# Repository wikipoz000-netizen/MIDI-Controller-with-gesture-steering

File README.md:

English below
# MIDI DJ Controller z kontrolą gestami

Projekt przedstawia autorski kontroler MIDI DJ wzbogacony o eksperymentalny system sterowania gestami. Urządzenie zostało opracowane w ramach pracy inżynierskiej na kierunku **Automatyka i Robotyka**.

## Opis projektu

Urządzenie łączy tradycyjne elementy kontrolera DJ (fadery, pokrętła, koła jog, przyciski) z warstwą bezdotykowego sterowania gestami opartą na ultradźwiękowych czujnikach odległości.

Kontroler komunikuje się z komputerem poprzez interfejs **USB-MIDI** i jest w pełni kompatybilny z oprogramowaniem DJ-skim, takim jak **Mixxx**.

## Sprzęt (Hardware)

Główne komponenty systemu:

* **Mikrokontroler:** Raspberry Pi Pico (RP2040)
* **Wejścia analogowe:** Multiplekser ADC (rozszerzenie liczby kanałów analogowych)
* **Wejścia cyfrowe:** Ekspander GPIO (dodatkowe wejścia dla przycisków)
* **Detekcja gestów:** Ultradźwiękowe czujniki odległości
* **Interfejs dotykowy:** Pojemnościowe czujniki dotyku
* **Konstrukcja:** Dedykowana płytka PCB oraz obudowa wykonana w technologii druku 3D

Pełna dokumentacja sprzętowa, schematy oraz projekty PCB znajdują się w katalogu `/hardware`.

## Oprogramowanie układowe (Firmware)

Firmware odpowiada za:

* Odczyt i filtrowanie sygnałów z wejść analogowych i cyfrowych.
* Skalowanie sygnałów i eliminację szumów.
* Interpretację danych z czujników na konkretne gesty.
* Generowanie komunikatów MIDI (**Note On/Off, Control Change, Pitch Bend**).
* Komunikację USB-MIDI o niskim opóźnieniu.

Kod źródłowy dostępny jest w katalogu `/firmware`.

## Integracja z oprogramowaniem

Kontroler został przetestowany z oprogramowaniem **Mixxx**. W repozytorium znajdują się niezbędne pliki mapowania MIDI (formaty `.xml` oraz `.js`).

## Zawartość repozytorium

* **Hardware:** Schematy ideowe i projekty płytek drukowanych.
* **Firmware:** Kod źródłowy mikrokontrolera.
* **Mapping:** Pliki konfiguracyjne MIDI dla oprogramowania DJ.
* **Dokumentacja:** Wyniki testów i specyfikacja techniczna.

---

# MIDI DJ Controller with Gesture Control

This project presents a custom-built MIDI DJ controller enhanced with an experimental gesture control system.  
It was developed as part of an engineering thesis in Robotics and Automation.

## Project Description

The device combines traditional DJ controller elements (faders, knobs, jog wheels, buttons) with a contactless gesture control layer based on ultrasonic distance sensors.

The controller communicates with a computer via USB-MIDI and is compatible with DJ software such as Mixxx.

## Hardware

Main components:

- Raspberry Pi Pico (RP2040)
- ADC multiplexer (for extended analog inputs)
- GPIO expander (for additional digital inputs)
- Ultrasonic distance sensors (gesture detection)
- Capacitive touch sensing
- Custom-designed PCB
- 3D-printed enclosure

All hardware schematics and PCB files are available in the `/hardware` directory.

## Firmware

The firmware is responsible for:

- Reading analog and digital inputs
- Signal filtering and scaling
- Gesture interpretation
- Generating MIDI messages (Note On/Off, Control Change, Pitch Bend)
- USB-MIDI communication

Source code is available in the `/firmware` directory.

## Software Integration

The controller was tested with Mixxx DJ software.  
The repository includes MIDI mapping files (XML and JS).

## Repository Contents

- Hardware schematics
- PCB design files
- Firmware source code
- MIDI mapping configuration
- Documentation and test results

---
## Licencja

Ten projekt jest udostępniony na licencji **Creative Commons Zero**. 
Więcej informacji w pliku [LICENSE](LICENSE).

## Autor

Wiktor Pozarzycki  
Praca inżynierska – 2026

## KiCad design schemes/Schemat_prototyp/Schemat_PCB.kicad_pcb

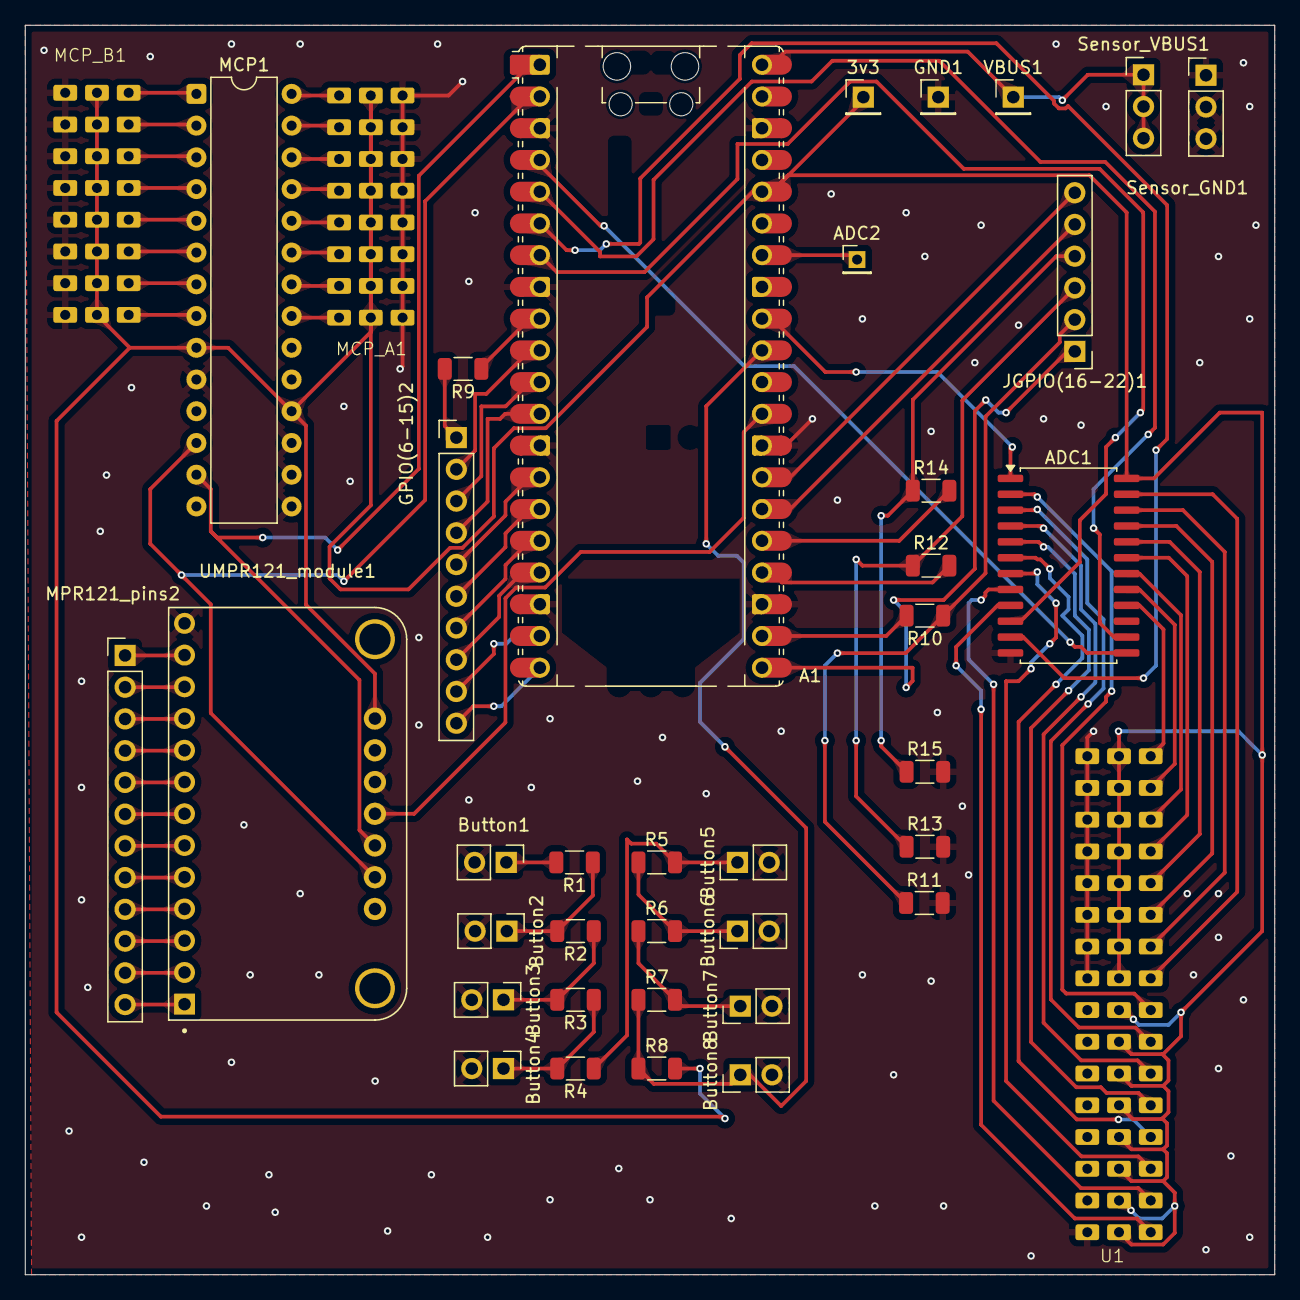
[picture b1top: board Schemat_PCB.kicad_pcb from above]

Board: 2 copper layers, 100.0 x 100.0 mm, 39 parts (0 on the bottom side), 84 nets.

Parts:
3v3: Conn_01x01_Pin; PinHeader_1x01_P2.54mm_Vertical
A1: RaspberryPi_Pico; RaspberryPi_Pico_Common_Unspecified
ADC1: CD74HC4067M; SOIC-24W_7.5x15.4mm_P1.27mm
ADC2: Conn_01x01_Pin; PinHeader_1x01_P2.00mm_Vertical
Button1, Button2, Button3, Button4, Button5, Button6, Button7, Button8: Conn_01x02_Pin; PinHeader_1x02_P2.54mm_Vertical
GND1: Conn_01x01_Pin; PinHeader_1x01_P2.54mm_Vertical
GPIO(6-15)2: Conn_01x10_Pin; PinHeader_1x10_P2.54mm_Vertical
JGPIO(16-22)1: Conn_01x06_Pin; PinHeader_1x06_P2.54mm_Vertical
MCP1: MCP23017_SP; DIP-28_W7.62mm
MCP_A1: PinHeader_3x8_2.54mm_MIRROR
MCP_B1: PinHeader_3x8_2.54mm_MIRROR
MPR121_pins2: Conn_01x12_Pin; PinHeader_1x12_P2.54mm_Vertical
R1: 15k; R_1206_3216Metric
R2: 7.5k; R_1206_3216Metric
R3: 4.7k; R_1206_3216Metric
R4: 3k; R_1206_3216Metric
R5: 2.2k; R_1206_3216Metric
R6: 1.6k; R_1206_3216Metric
R7: 1.2k; R_1206_3216Metric
R8: 10k; R_1206_3216Metric
R9: 330; R_1206_3216Metric
R10, R12, R14: 1k; R_1206_3216Metric
R11, R13, R15: 2k; R_1206_3216Metric
Sensor_GND1: Conn_01x03_Pin; PinHeader_1x03_P2.54mm_Vertical
Sensor_VBUS1: Conn_01x03_Pin; PinHeader_1x03_P2.54mm_Vertical
U1: PinHeader_3x16_2.54mm
UMPR121_module1: 1982; MODULE_1982
VBUS1: Conn_01x01_Pin; PinHeader_1x01_P2.54mm_Vertical

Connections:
GND: A1.3 (GND), A1.8 (GND), A1.13 (GND), A1.18 (GND), A1.23 (GND), A1.28 (GND), A1.38 (GND), ADC1.12 (GND), Button1.2, Button2.2, Button3.2, Button4.2, Button5.2, Button6.2, Button7.2, Button8.2, GND1.1, MCP1.10 (VSS), MCP1.15 (A0), MCP1.16 (A1), MCP1.17 (A2), MCP_A1.17 (GND), MCP_A1.18 (GND), MCP_A1.19 (GND), MCP_A1.20 (GND), MCP_A1.21 (GND), MCP_A1.22 (GND), MCP_A1.23 (GND), MCP_A1.24 (GND), MCP_B1.17 (GND), MCP_B1.18 (GND), MCP_B1.19 (GND), MCP_B1.20 (GND), MCP_B1.21 (GND), MCP_B1.22 (GND), MCP_B1.23 (GND), MCP_B1.24 (GND), R11.2, R13.2, R15.2, Sensor_GND1.1, Sensor_GND1.2, Sensor_GND1.3, U1.33 (GND), U1.34 (GND), U1.35 (GND), U1.36 (GND), U1.37 (GND), U1.38 (GND), U1.39 (GND), U1.40 (GND), U1.41 (GND), U1.42 (GND), U1.43 (GND), U1.44 (GND), U1.45 (GND), U1.46 (GND), U1.47 (GND), U1.48 (GND), UMPR121_module1.JP1_13 (GND), UMPR121_module1.JP2_3 (GND)
unnamed: 3v3.1, A1.36 (3V3), ADC1.24 (VCC), MCP1.9 (VDD), MCP1.18 (~RESET), MCP_A1.9 (VCC), MCP_A1.10 (VCC), MCP_A1.11 (VCC), MCP_A1.12 (VCC), MCP_A1.13 (VCC), MCP_A1.14 (VCC), MCP_A1.15 (VCC), MCP_A1.16 (VCC), MCP_B1.9 (VCC), MCP_B1.10 (VCC), MCP_B1.11 (VCC), MCP_B1.12 (VCC), MCP_B1.13 (VCC), MCP_B1.14 (VCC), MCP_B1.15 (VCC), MCP_B1.16 (VCC), R8.2, U1.17 (VCC), U1.18 (VCC), U1.19 (VCC), U1.20 (VCC), U1.21 (VCC), U1.22 (VCC), U1.23 (VCC), U1.24 (VCC), U1.25 (VCC), U1.26 (VCC), U1.27 (VCC), U1.28 (VCC), U1.29 (VCC), U1.30 (VCC), U1.31 (VCC), U1.32 (VCC), UMPR121_module1.JP2_1 (VIN)
unnamed: A1.1 (GPIO0), MCP1.13 (SDA), UMPR121_module1.JP2_5 (SDA)
unnamed: A1.2 (GPIO1), MCP1.12 (SCK), UMPR121_module1.JP2_6 (SCL)
unnamed: A1.4 (GPIO2), ADC1.13 (S3)
unnamed: A1.5 (GPIO3), ADC1.14 (S2)
unnamed: A1.6 (GPIO4), ADC1.11 (S1)
unnamed: A1.7 (GPIO5), ADC1.10 (S0)
unnamed: A1.9 (GPIO6), R9.1
unnamed: A1.10 (GPIO7), GPIO(6-15)2.2
unnamed: A1.11 (GPIO8), GPIO(6-15)2.3
unnamed: A1.12 (GPIO9), GPIO(6-15)2.4
unnamed: A1.14 (GPIO10), GPIO(6-15)2.5
unnamed: A1.15 (GPIO11), GPIO(6-15)2.6
unnamed: A1.16 (GPIO12), GPIO(6-15)2.7
unnamed: A1.17 (GPIO13), GPIO(6-15)2.8
unnamed: A1.19 (GPIO14), GPIO(6-15)2.9
unnamed: A1.20 (GPIO15), GPIO(6-15)2.10
unnamed: A1.21 (GPIO16), JGPIO(16-22)1.1
unnamed: A1.22 (GPIO17), R10.2
unnamed: A1.24 (GPIO18), R12.2
unnamed: A1.25 (GPIO19), R14.2
unnamed: A1.26 (GPIO20), JGPIO(16-22)1.5
unnamed: A1.27 (GPIO21), JGPIO(16-22)1.6
unnamed: A1.29 (GPIO22), UMPR121_module1.JP2_4 (ADDR)
unnamed: A1.31 (GPIO26_ADC0), Button8.1, R7.1, R8.1
unnamed: A1.32 (GPIO27_ADC1), ADC1.1 (COM)
unnamed: A1.34 (GPIO28_ADC2), ADC2.1
unnamed: A1.40 (VBUS), Sensor_VBUS1.1, Sensor_VBUS1.2, Sensor_VBUS1.3, VBUS1.1
unnamed: ADC1.9 (I0), U1.1 (A1)
unnamed: ADC1.8 (I1), U1.2 (A2)
unnamed: ADC1.7 (I2), U1.3 (A3)
unnamed: ADC1.6 (I3), U1.4 (A4)
unnamed: ADC1.5 (I4), U1.5 (A5)
unnamed: ADC1.4 (I5), U1.6 (A6)
unnamed: ADC1.3 (I6), U1.7 (A7)
unnamed: ADC1.2 (I7), U1.8 (A8)
unnamed: ADC1.23 (I8), U1.9 (A9)
unnamed: ADC1.22 (I9), U1.10 (A10)
unnamed: ADC1.21 (I10), U1.11 (A11)
unnamed: ADC1.20 (I11), U1.12 (A12)
unnamed: ADC1.19 (I12), U1.13 (A13)
unnamed: ADC1.18 (I13), U1.14 (A14)
unnamed: ADC1.17 (I14), U1.15 (A15)
unnamed: ADC1.16 (I15), U1.16 (A16)
unnamed: Button1.1, R1.2
unnamed: Button2.1, R1.1, R2.2
unnamed: Button3.1, R2.1, R3.2
unnamed: Button4.1, R3.1, R4.2
unnamed: Button5.1, R4.1, R5.2
unnamed: Button6.1, R5.1, R6.2
unnamed: Button7.1, R6.1, R7.2
unnamed: GPIO(6-15)2.1, R9.2
unnamed: JGPIO(16-22)1.2, R10.1, R11.1
unnamed: JGPIO(16-22)1.3, R12.1, R13.1
unnamed: JGPIO(16-22)1.4, R14.1, R15.1
unnamed: MCP1.21 (GPA0), MCP_A1.1 (A1)
unnamed: MCP1.22 (GPA1), MCP_A1.2 (A2)
unnamed: MCP1.23 (GPA2), MCP_A1.3 (A3)
unnamed: MCP1.24 (GPA3), MCP_A1.4 (A4)
unnamed: MCP1.25 (GPA4), MCP_A1.5 (A5)
unnamed: MCP1.26 (GPA5), MCP_A1.6 (A6)
unnamed: MCP1.27 (GPA6), MCP_A1.7 (A7)
unnamed: MCP1.28 (GPA7), MCP_A1.8 (A8)
unnamed: MCP1.1 (GPB0), MCP_B1.1 (A1)
unnamed: MCP1.2 (GPB1), MCP_B1.2 (A2)
unnamed: MCP1.3 (GPB2), MCP_B1.3 (A3)
unnamed: MCP1.4 (GPB3), MCP_B1.4 (A4)
unnamed: MCP1.5 (GPB4), MCP_B1.5 (A5)
unnamed: MCP1.6 (GPB5), MCP_B1.6 (A6)
unnamed: MCP1.7 (GPB6), MCP_B1.7 (A7)
unnamed: MCP1.8 (GPB7), MCP_B1.8 (A8)
unnamed: MPR121_pins2.1, UMPR121_module1.JP1_12 (ELEC0)
unnamed: MPR121_pins2.2, UMPR121_module1.JP1_11 (ELEC1)
unnamed: MPR121_pins2.3, UMPR121_module1.JP1_10 (ELEC2)
unnamed: MPR121_pins2.4, UMPR121_module1.JP1_9 (ELEC3)
unnamed: MPR121_pins2.5, UMPR121_module1.JP1_8 (ELEC4)
unnamed: MPR121_pins2.6, UMPR121_module1.JP1_7 (ELEC5)
unnamed: MPR121_pins2.7, UMPR121_module1.JP1_6 (ELEC6)
unnamed: MPR121_pins2.8, UMPR121_module1.JP1_5 (ELEC7)
unnamed: MPR121_pins2.9, UMPR121_module1.JP1_4 (ELEC8)
unnamed: MPR121_pins2.10, UMPR121_module1.JP1_3 (ELEC9)
unnamed: MPR121_pins2.11, UMPR121_module1.JP1_2 (ELEC10)
unnamed: MPR121_pins2.12, UMPR121_module1.JP1_1 (ELEC11)

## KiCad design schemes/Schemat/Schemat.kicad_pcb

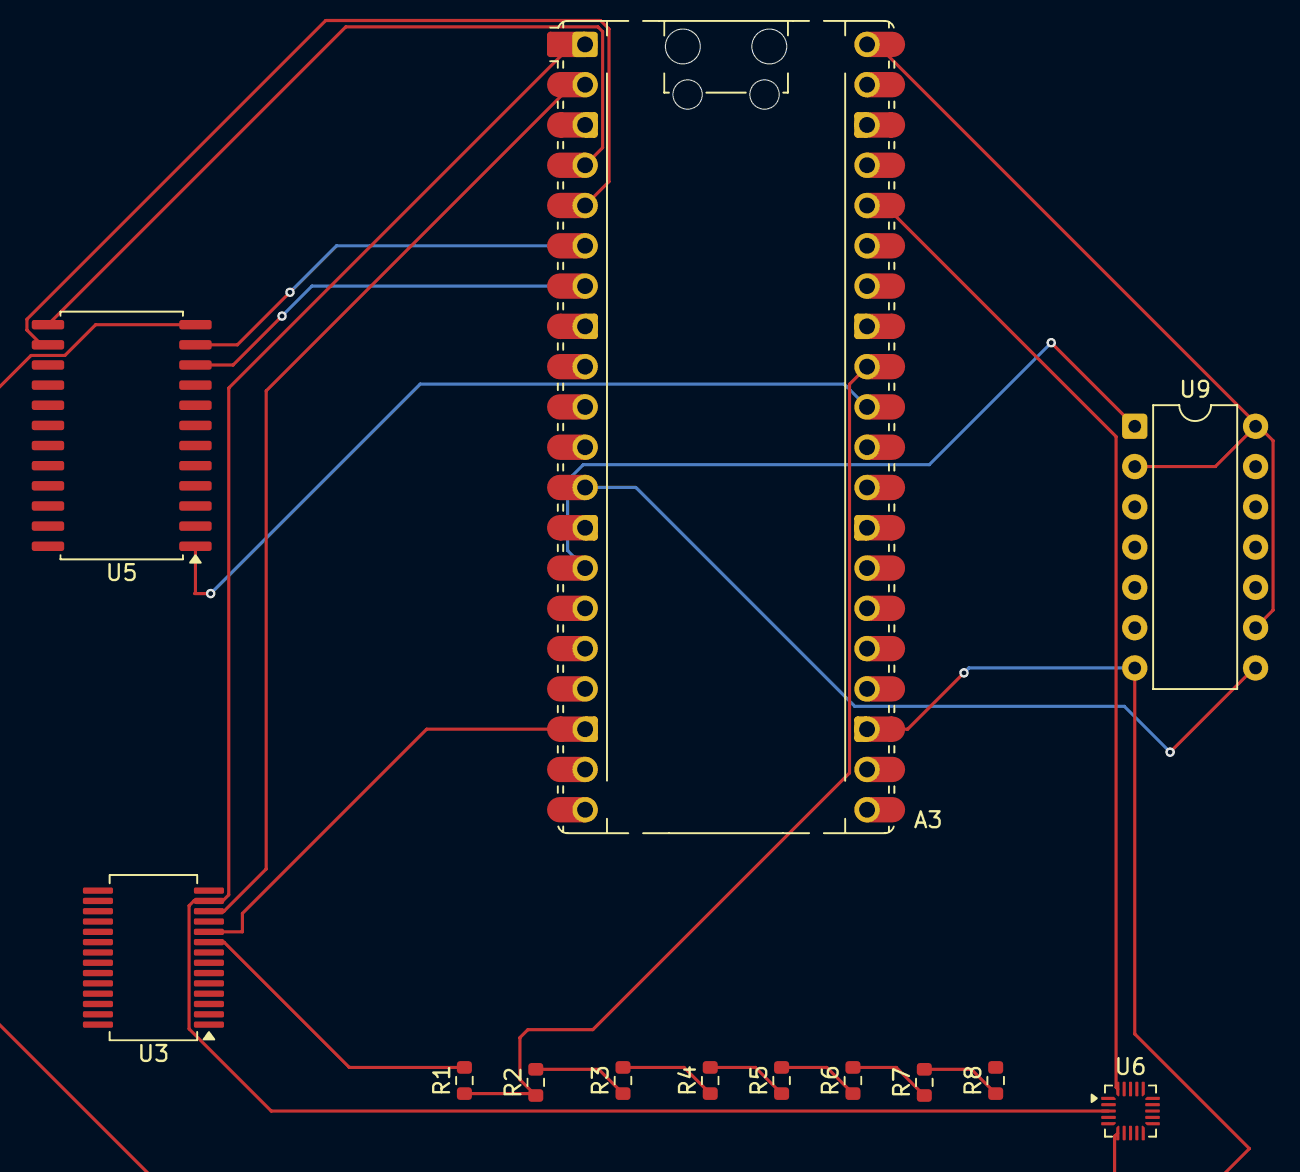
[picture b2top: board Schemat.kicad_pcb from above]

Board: 2 copper layers, 13 parts (0 on the bottom side), 19 nets.

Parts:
A3: RaspberryPi_Pico; RaspberryPi_Pico_Common_Unspecified
R1: 10k; R_0603_1608Metric
R2: 1.2k; R_0603_1608Metric
R3: 1.6k; R_0603_1608Metric
R4: 2.2k; R_0603_1608Metric
R5: 3k; R_0603_1608Metric
R6: 4.7k; R_0603_1608Metric
R7: 7.5k; R_0603_1608Metric
R8: 15k; R_0603_1608Metric
U3: MCP23017_SS; SSOP-28_5.3x10.2mm_P0.65mm
U5: CD74HC4067M; SOIC-24W_7.5x15.4mm_P1.27mm
U6: MPR121QR2; UQFN-20_3x3mm_P0.4mm
U9: 74HCT164; DIP-14_W7.62mm

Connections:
unnamed: A3.36 (3V3), R1.2, U3.9 (VDD), U5.24 (VCC), U6.20 (VDD)
unnamed: A3.1 (GPIO0), U3.13 (SDA), U6.3 (SDA)
unnamed: A3.2 (GPIO1), U3.12 (SCK), U6.2 (SCL)
unnamed: A3.4 (GPIO2), U5.13 (S3)
unnamed: A3.5 (GPIO3), U5.14 (S2)
unnamed: A3.6 (GPIO4), U5.11 (S1)
unnamed: A3.7 (GPIO5), U5.10 (S0)
unnamed: A3.12 (GPIO9), U9.8 (CP)
unnamed: A3.14 (GPIO10), U9.1 (DSA)
unnamed: A3.31 (GPIO26_ADC0), U5.1 (COM)
unnamed: A3.32 (GPIO27_ADC1), R1.1, R2.1
unnamed: A3.40 (VBUS), U9.2 (DSB), U9.9 (~MR), U9.14 (VCC)
unnamed: R2.2, R3.1
unnamed: R3.2, R4.1
unnamed: R4.2, R5.1
unnamed: R5.2, R6.1
unnamed: R6.2, R7.1
unnamed: R7.2, R8.1
unnamed: A3.3 (GND), A3.8 (GND), A3.13 (GND), A3.18 (GND), A3.23 (GND), A3.28 (GND), A3.38 (GND), U3.10 (VSS), U5.12 (GND), U6.6 (VSS), U9.7 (GND)

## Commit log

2026-02-17 Update README with project overview and features
    Expanded project details, features, and context for the MIDI controller with gesture control system.
2026-02-17 Add DJC-DIY JOG TEST MIDI controller preset
    This commit adds a new MIDI controller preset for the DJC-DIY JOG TEST, defining various controls and their MIDI mappings.
2026-02-17 Create SourceCodes
2026-02-17 Create Case
2026-02-17 Create k
2026-02-17 Create f
2026-03-03 Update README with license and author information
    Add license information and author details to README
2026-03-03 Add CC0 1.0 Universal license
    Added the CC0 1.0 Universal license to the project.
